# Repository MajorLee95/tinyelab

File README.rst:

++++++++++++++++++++++++++++++++++++++++++++++++++++++++++++++++++++++++++++++++++++++++++++++++++++
Tiny E-LAB
++++++++++++++++++++++++++++++++++++++++++++++++++++++++++++++++++++++++++++++++++++++++++++++++++++

:Auteur:               Le VoLab : MajorLee
:Site_Web:             http://www.vorobotics.com/
:Projet:               Tiny e-LAB my contrib.
:Version:              2022
:documentation:        https://majorlee95.github.io/tinyelab
:Licence:              CC0 4.0
:Liens:                https://creativecommons.org/licenses

Ce projet est ma contribution au `Projet Tiny e-lab de MarcLuer sur Thyngiverse`_

Pour plus d'informations suivre le liens documantation ci-dessus !!!!!

.. _`Projet Tiny e-lab de MarcLuer sur Thyngiverse`: https://www.thingiverse.com/thing:2999383

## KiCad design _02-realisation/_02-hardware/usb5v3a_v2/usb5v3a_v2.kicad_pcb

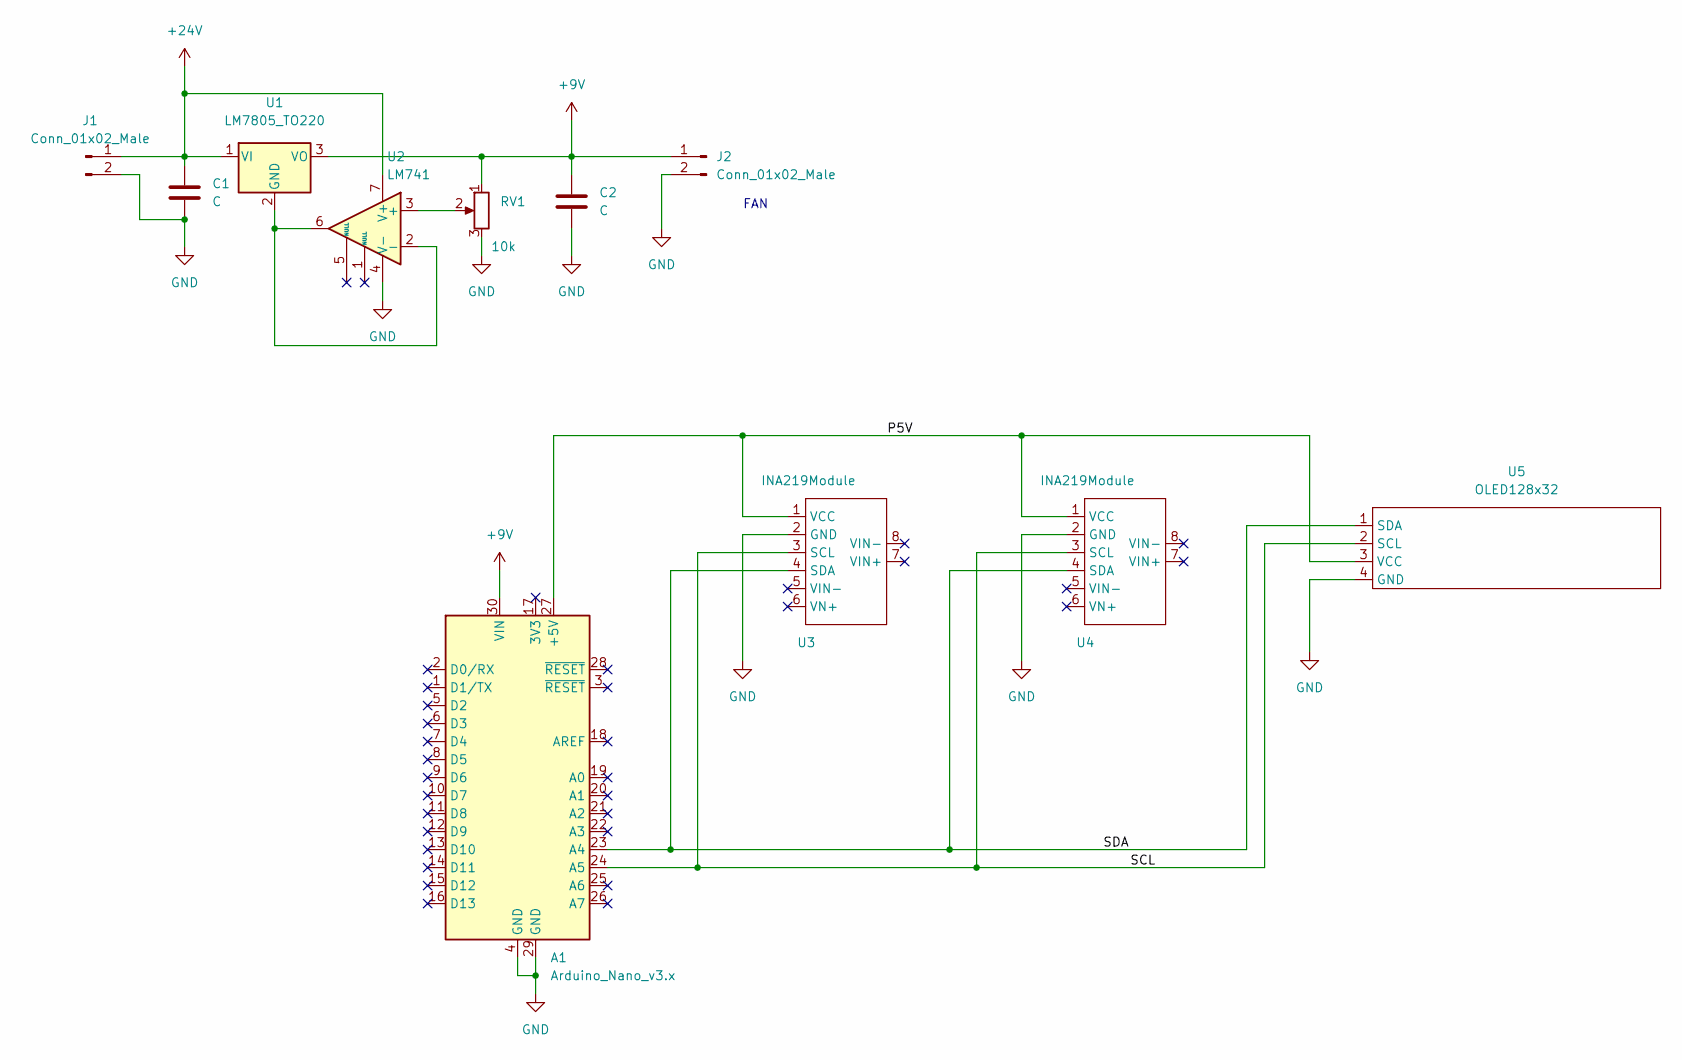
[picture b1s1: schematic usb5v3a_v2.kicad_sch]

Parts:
A1: Arduino_Nano_v3.x; Arduino_Nano
C1, C2: C; C_Disc_D3.0mm_W1.6mm_P2.50mm
J1, J2: Conn_01x02_Male; PinHeader_1x02_P2.54mm_Vertical
RV1: 10k; Potentiometer_Piher_PT-10-V10_Vertical
U1: LM7805_TO220; TO-220-3_Vertical
U2: LM741; DIP-8_W7.62mm
U3, U4: INA219Module; INA219
U5: OLED128x32

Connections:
+9V: A1.30 (VIN), C2.1, J2.1, RV1.1, U1.3 (VO)
+24V: C1.1, J1.1, U1.1 (VI), U2.7 (V+)
/P5V: A1.27 (+5V), U3.1 (VCC), U4.1 (VCC), U5.3 (VCC)
/SCL: A1.24 (A5), U3.3 (SCL), U4.3 (SCL), U5.2 (SCL)
/SDA: A1.23 (A4), U3.4 (SDA), U4.4 (SDA), U5.1 (SDA)
GND: A1.4 (GND), A1.29 (GND), C1.2, C2.2, J1.2, J2.2, RV1.3, U2.4 (V-), U3.2 (GND), U4.2 (GND), U5.4 (GND)
unnamed: RV1.2, U2.3 (+)
unnamed: U1.2 (GND), U2.2 (-), U2.6

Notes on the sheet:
FAN

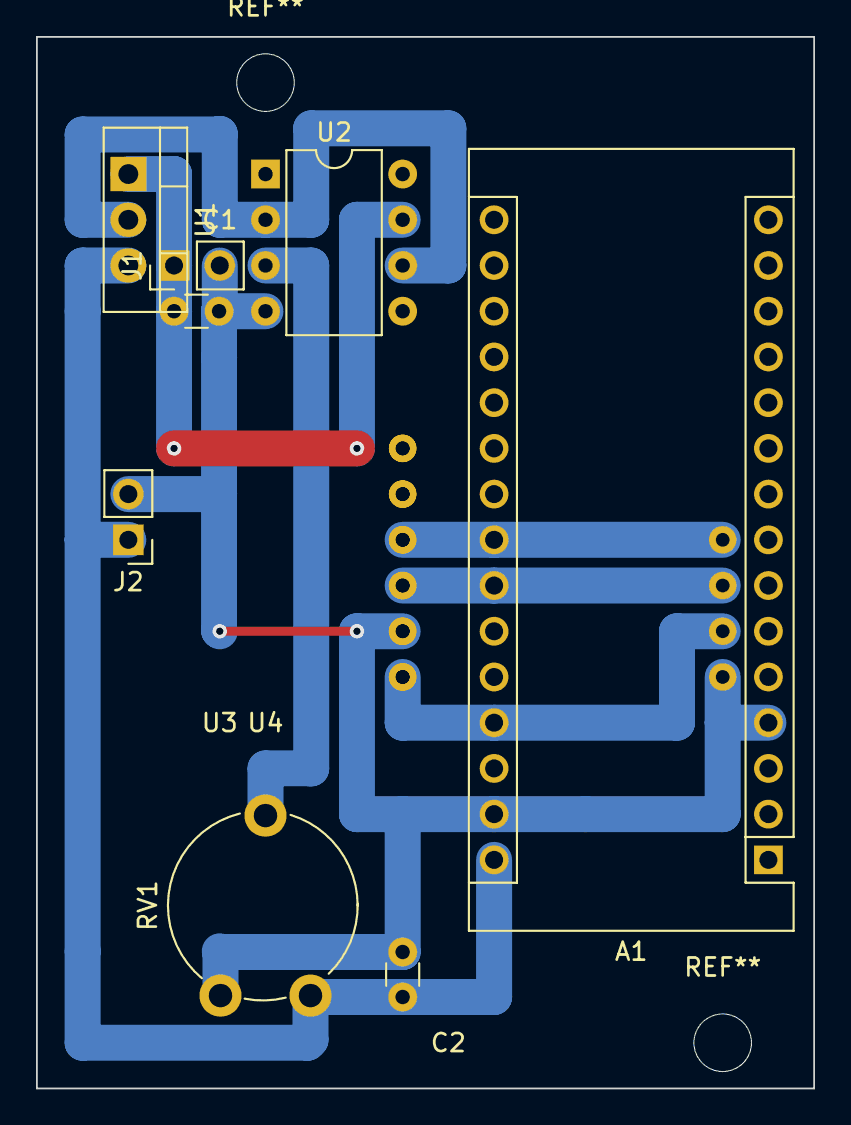
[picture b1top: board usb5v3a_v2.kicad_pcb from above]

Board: 2 copper layers, 43.2 x 58.4 mm, 11 parts (1 on the bottom side), 8 nets.

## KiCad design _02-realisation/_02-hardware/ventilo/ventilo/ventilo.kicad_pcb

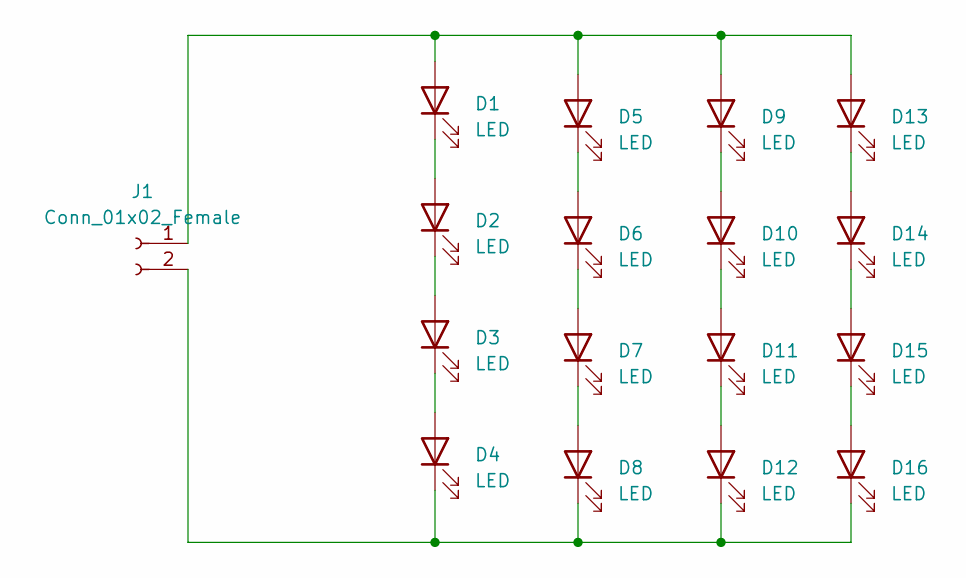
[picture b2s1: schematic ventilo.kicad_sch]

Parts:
D1, D2, D3, D4, D5, D6, D7, D8, D9, D10, D11, D12, D13, D14, D15, D16: LED; LED_D5.0mm
J1: Conn_01x02_Female; PinHeader_1x02_P2.54mm_Horizontal

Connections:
unnamed: D1.1 (K), D2.2 (A)
unnamed: D1.2 (A), D5.2 (A), D9.2 (A), D13.2 (A), J1.1
unnamed: D2.1 (K), D3.2 (A)
unnamed: D3.1 (K), D4.2 (A)
unnamed: D5.1 (K), D6.2 (A)
unnamed: D6.1 (K), D7.2 (A)
unnamed: D7.1 (K), D8.2 (A)
unnamed: D10.1 (K), D11.2 (A)
unnamed: D9.1 (K), D10.2 (A)
unnamed: D11.1 (K), D12.2 (A)
unnamed: D4.1 (K), D8.1 (K), D12.1 (K), D16.1 (K), J1.2
unnamed: D13.1 (K), D14.2 (A)
unnamed: D14.1 (K), D15.2 (A)
unnamed: D15.1 (K), D16.2 (A)

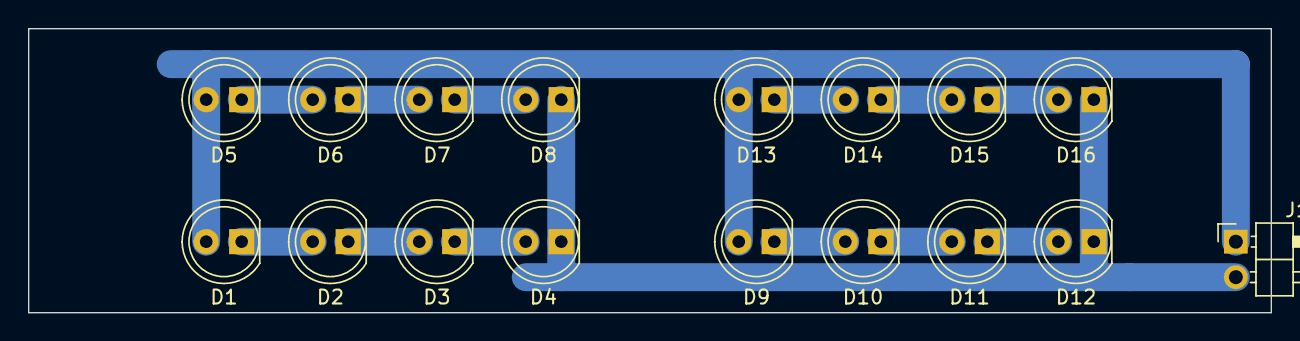
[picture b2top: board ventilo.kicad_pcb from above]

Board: 2 copper layers, 88.9 x 20.3 mm, 17 parts (0 on the bottom side), 14 nets.

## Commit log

2022-04-17 premier commit, il était temps!
2022-04-17 doc module oscillo 9V
2022-04-20 ajout voltAmperemetre
2022-04-23 add gene function + retouche outillageXT + code opoulet pour exemple scoop
2022-04-24 Alim triple et amperemtre analogique début
2022-04-29 module ventilo en cours
2022-04-29 ventilo en cours
2022-04-29 ajout README
2022-04-29 mise à ajour .ignore
2022-04-29 remove rush
2022-04-29 ajout lien vers Orginal
2022-05-02 fan support en cours
2022-05-04 quelques retouches mineurs
2022-05-23 fan system en cours version aimant prête pour une première impression
2022-05-25 design casquette fan support ok
2022-05-27 version aimant testée KO
2022-05-27 mise à jour avancement avec donnée branche aimantsEnLong
2022-05-30 juste une maj avancement module 3.3v,5 +12-12
2022-06-22 fichier 028 créé rebase
2022-06-22 poignee et languette dessinnees, raf encoche et plots
2022-06-22 languette version 2 en cours de test
2022-06-22 reprise poignee et languette module ventilo RAF encoche
2022-06-22 potar en cours d'ajout sur la partie mobile
2022-06-22 retour à un potar normal + un switch
2022-06-22 les finissions du modul ventilo
2022-06-22 retour sur main pour les finisiions
2022-06-22 odul ventilo terminé hors test
2022-06-22 impressions en cours
2022-06-22 remonté d'un fichier cura pour servir de ref
2022-07-02 Module ventilo imprimé
2022-07-04 premier commit de doc
2022-07-04 nojekill
2022-07-04 nojekyll
2022-07-04 nojekyll troisième
2022-07-04 nojekyll ça roule
2022-07-04 maj date
2022-07-06 xt60 cover + correction Muthex to Ruthex
2022-07-06 xt60 cover
2022-07-06 rouge
2022-07-13 XT60 cover OK + ventilo update
2022-07-16 principalement nome ventilo en cours
2022-07-16 update avancement
2022-08-03 module lidl e cours
2022-08-03 module lidl wip
2022-08-10 Nomenclature module VA
2022-08-10 nomenclature VA
2022-08-14 wiki du lab
2022-08-14 projet dans le wiki du lab
2022-08-14 module pakside ok
2022-08-14 parkside ok
2022-08-15 modi=ole de base en v12
2022-08-15 base v012
2022-09-10 module USB3A new
2022-09-17 USB 2x 3A v2 en cours (encoche PCB)
2022-10-08 USB 2x 3A v2 presque fini
2022-10-08 doc usb éx 3A v2
2022-10-12 usb 2x 3A en doc en cours
2022-10-12 usb 2x 3A en cours de doc
2022-10-22 Mise à jour documentaire usb2x3a
2022-10-22 USB 2x 3A v2 grosse maj doc
2022-10-22 nettoyage dossier + usb2x3a maj modèle freecad
2022-10-22 lien vers le lab...
2022-10-29 Doc module ventilo nomenclature
2022-10-29 ventilo ajout photo
2022-11-09 Documentation ventilo terminée
2022-11-09 doc module ventilo ok
2022-11-09 Triple tiny voltmètre complément de doc
2022-11-09 complément doc 3 voltmètres
2022-11-12 introduction de volabid.rst
2022-11-23 module Oscillo introduction des entretoises + elements commun visTHCMixj full parametrique
2022-11-23 CPAOToSCILLO en cours de design
2022-12-10 Ajout ref fer à souder
2022-12-10 ajout photo fer
2022-12-10 ajout fer insert
2024-03-09 ajout support TS-100 alternatif...
2024-03-09 add TS-100 support alternate
2024-03-09 Racourcir Les Noms De Certains Fichier
2024-03-12 moduleUSB2 voies simple en cours
2024-03-21 Module USB 2x3A ok
